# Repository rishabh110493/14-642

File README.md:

# 14-642
Work Done in Embedded Systems as a part of course

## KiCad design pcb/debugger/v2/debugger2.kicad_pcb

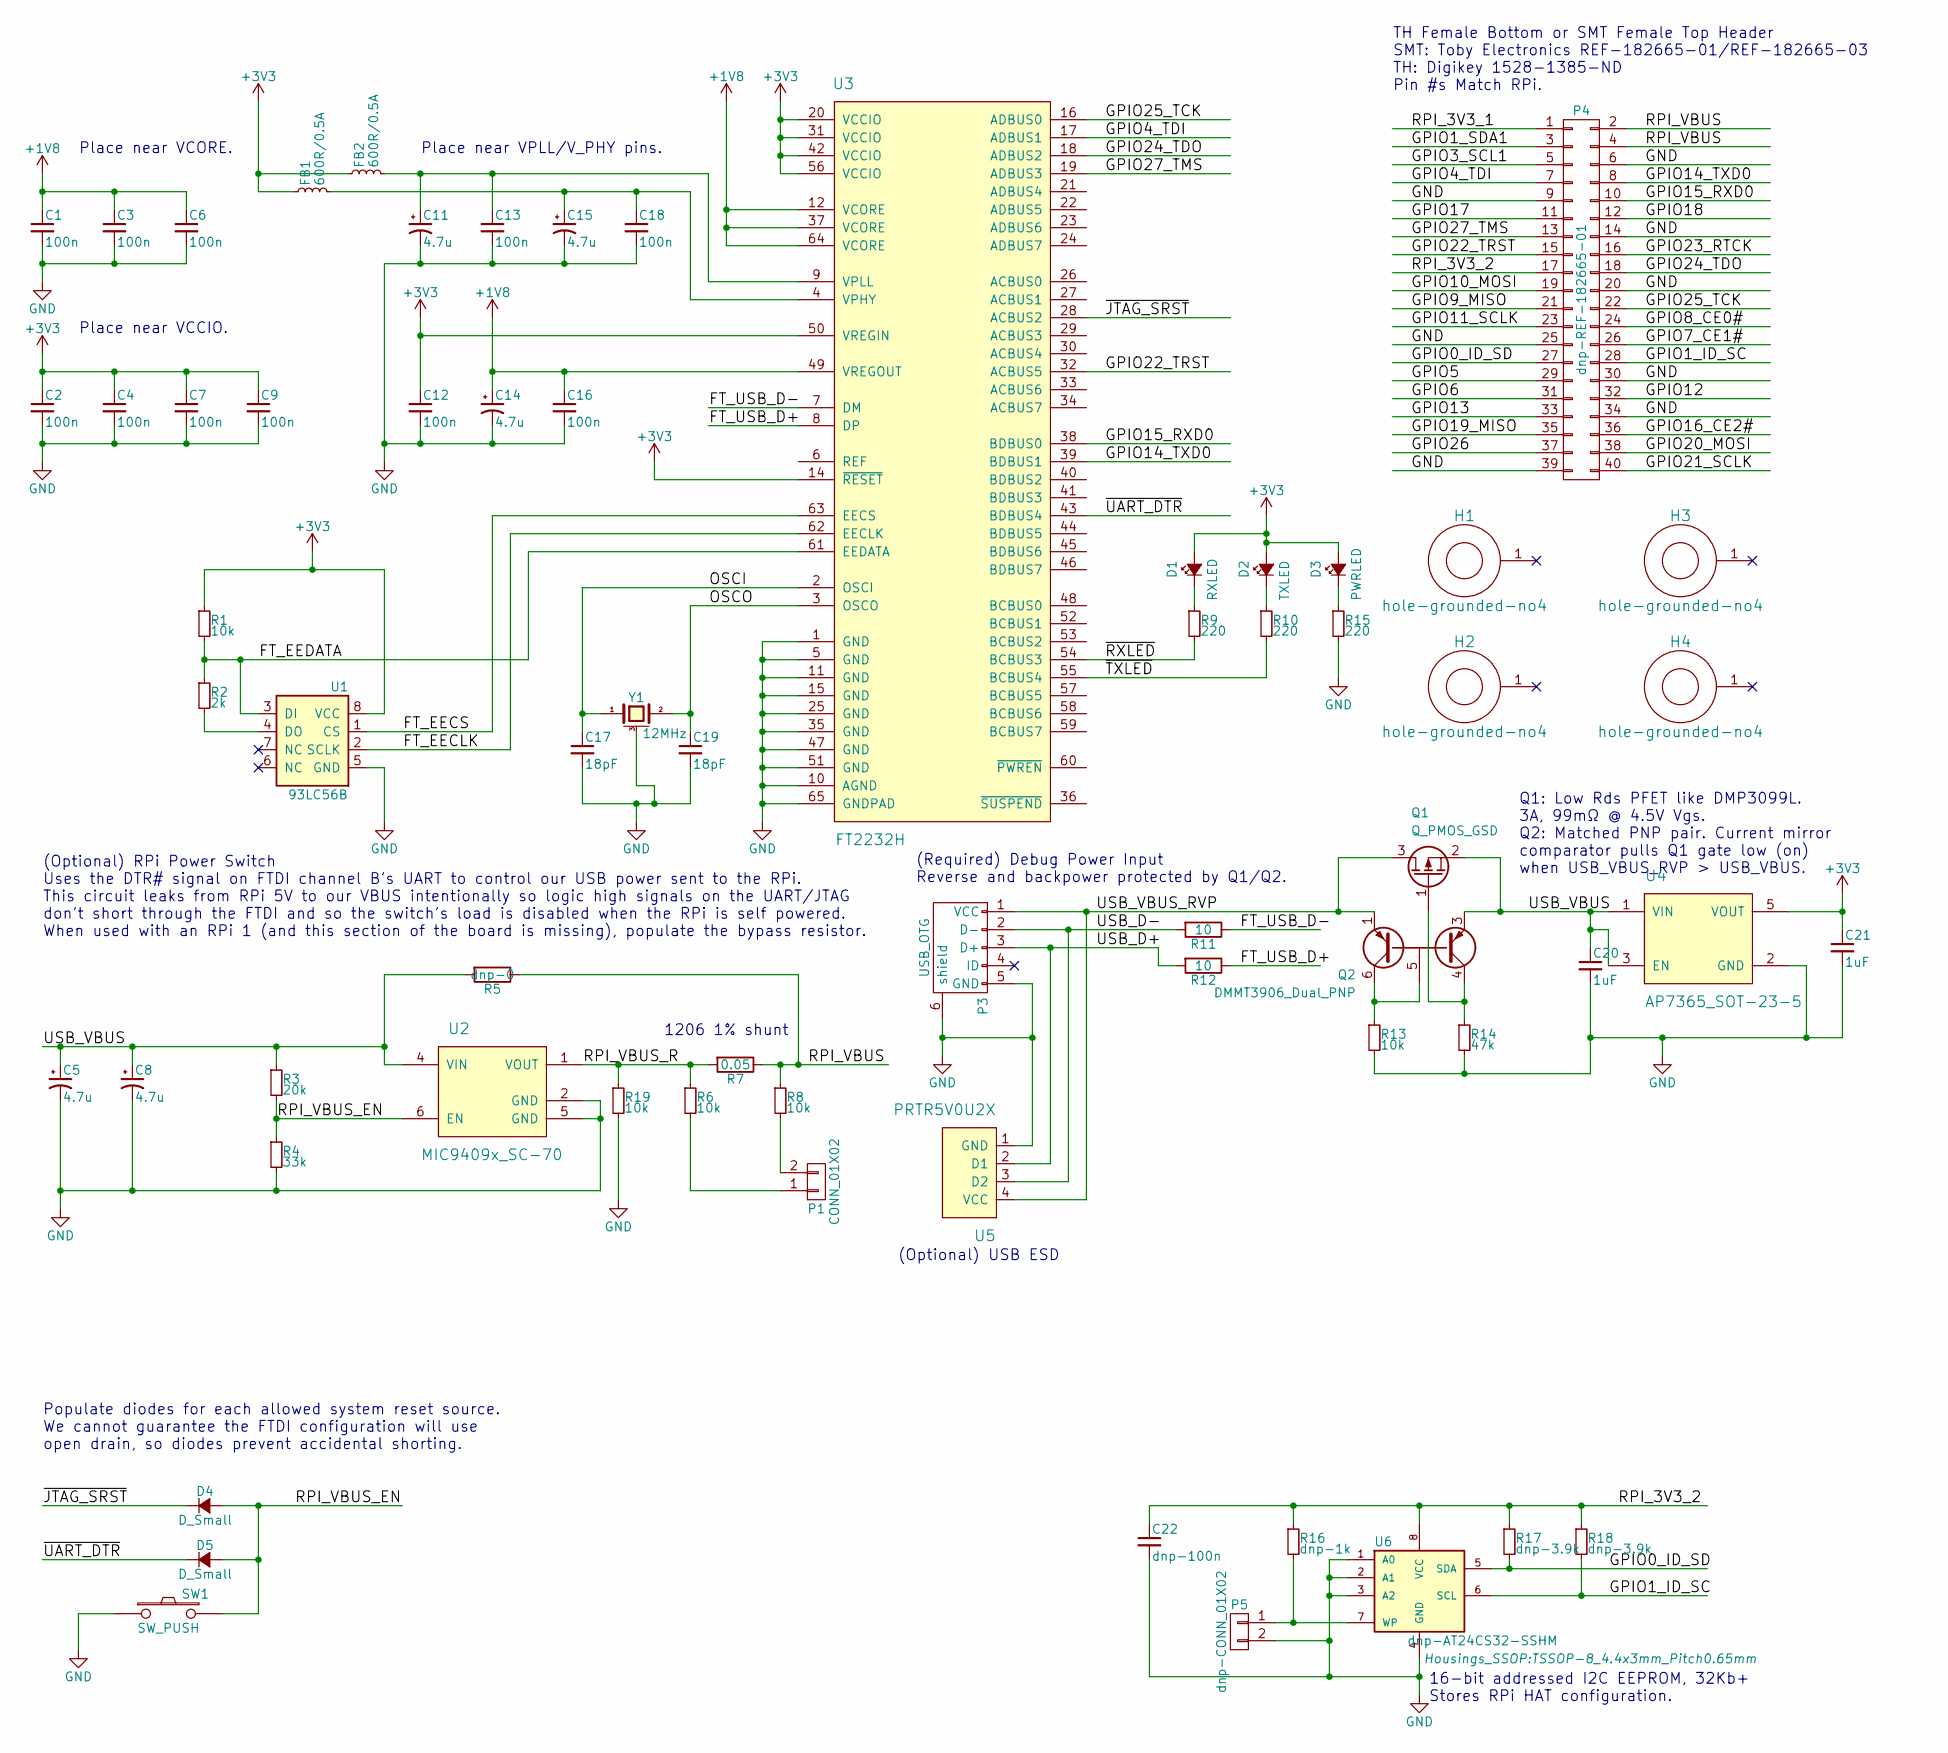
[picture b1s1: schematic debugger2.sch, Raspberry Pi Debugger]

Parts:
C1, C2, C3, C4, C6, C7, C9, C12, C13, C16, C18: 100n; C_0603
C5, C8, C11, C14, C15: 4.7u; C_1206
C17, C19: 18pF; C_0603
C20, C21: 1uF; C_0603
C22: dnp-100n; C_0603
D1: RXLED; LED-0603
D2: TXLED; LED-0603
D3: PWRLED; LED-0603
D4, D5: D_Small; SOD-523
FB1, FB2: 600R/0.5A; R_0805
H1, H2, H3, H4: hole-grounded-no4; hole-no4
P1: CONN_01X02; Pin_Header_Straight_1x02
P3: USB_OTG; USB_Micro-B_SMT
P4: dnp-REF-182665-01; Pin_Header_Straight_TH-SMT-NoPaste_2x20
P5: dnp-CONN_01X02; Pin_Header_Straight_1x02
Q1: Q_PMOS_GSD; SOT-23
Q2: DMMT3906_Dual_PNP; SOT-23-6
R1, R6, R8, R13, R19: 10k; R_0603
R2: 2k; R_0603
R3: 20k; R_0603
R4: 33k; R_0603
R5: dnp-0; R_0603
R7: 0.05; R_1206
R9, R10, R15: 220; R_0603
R11, R12: 10; R_0603
R14: 47k; R_0603
R16: dnp-1k; R_0603
R17, R18: dnp-3.9k; R_0603
SW1: SW_PUSH; SW_SPST_EVPBF
U1: 93LC56B; TSSOP-8_4.4x3mm_Pitch0.65mm
U2: MIC9409x_SC-70; SC-70-6
U3: FT2232H; TQFP-64_10x10mm_Pitch0.5mm
U4: AP7365_SOT-23-5; SOT-23-5
U5: PRTR5V0U2X; SOT-143_NXP
U6: dnp-AT24CS32-SSHM; TSSOP-8_4.4x3mm_Pitch0.65mm
Y1: 12MHz; Crystal_Grounded_3.2x2.5

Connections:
+1V8: C1.1, C3.1, C6.1, C14.1, C16.1, U3.12 (VCORE), U3.37 (VCORE), U3.49 (VREGOUT), U3.64 (VCORE)
+3V3: C2.1, C4.1, C7.1, C9.1, C12.1, C21.1, D1.2 (A), D2.2 (A), D3.2 (A), FB1.1, FB2.1, R1.1, U1.8 (VCC), U3.14 (~RESET), U3.20 (VCCIO), U3.31 (VCCIO), U3.42 (VCCIO), U3.50 (VREGIN), U3.56 (VCCIO), U4.5 (VOUT)
/FT_EECLK: U1.2 (SCLK), U3.62 (EECLK)
/FT_EECS: U1.1 (CS), U3.63 (EECS)
/FT_EEDATA: R1.2, R2.1, U1.3 (DI), U3.61 (EEDATA)
/FT_USB_D+: R12.1, U3.8 (DP)
/FT_USB_D-: R11.1, U3.7 (DM)
/GPIO0_ID_SD: P4.27, R17.2, U6.5 (SDA)
/GPIO1_ID_SC: P4.28, R18.2, U6.6 (SCL)
/GPIO1_SDA1: P4.3
/GPIO3_SCL1: P4.5
/GPIO4_TDI: P4.7, U3.17 (ADBUS1)
/GPIO5: P4.29
/GPIO6: P4.31
/GPIO7_CE1#: P4.26
/GPIO8_CE0#: P4.24
/GPIO9_MISO: P4.21
/GPIO10_MOSI: P4.19
/GPIO11_SCLK: P4.23
/GPIO12: P4.32
/GPIO13: P4.33
/GPIO14_TXD0: P4.8, U3.39 (BDBUS1)
/GPIO15_RXD0: P4.10, U3.38 (BDBUS0)
/GPIO16_CE2#: P4.36
/GPIO17: P4.11
/GPIO18: P4.12
/GPIO19_MISO: P4.35
/GPIO20_MOSI: P4.38
/GPIO21_SCLK: P4.40
/GPIO22_TRST: P4.15, U3.32 (ACBUS5)
/GPIO23_RTCK: P4.16
/GPIO24_TDO: P4.18, U3.18 (ADBUS2)
/GPIO25_TCK: P4.22, U3.16 (ADBUS0)
/GPIO26: P4.37
/GPIO27_TMS: P4.13, U3.19 (ADBUS3)
/OSCI: C17.1, U3.2 (OSCI), Y1.1
/OSCO: C19.1, U3.3 (OSCO), Y1.2
/RPI_3V3_1: P4.1
/RPI_3V3_2: C22.1, P4.17, R16.1, R17.1, R18.1, U6.8 (VCC)
/RPI_VBUS: P4.2, P4.4, R5.1, R7.1, R8.1
/RPI_VBUS_EN: D4.2 (A), D5.2 (A), R3.2, R4.1, SW1.2, U2.6 (EN)
/RPI_VBUS_R: R6.1, R7.2, R19.1, U2.1 (VOUT)
/USB_D+: P3.3 (D+), R12.2, U5.2 (D1)
/USB_D-: P3.2 (D-), R11.2, U5.3 (D2)
/USB_VBUS: C5.1, C8.1, C20.1, Q1.2 (S), Q2.3 (E2), R3.1, R5.2, U2.4 (VIN), U4.1 (VIN), U4.3 (EN)
/USB_VBUS_RVP: P3.1 (VCC), Q1.3 (D), Q2.1 (E1), U5.4 (VCC)
/~JTAG_SRST: D4.1 (K), U3.28 (ACBUS2)
/~RXLED: R9.2, U3.54 (BCBUS3)
/~TXLED: R10.2, U3.55 (BCBUS4)
/~UART_DTR: D5.1 (K), U3.43 (BDBUS4)
GND: C1.2, C2.2, C3.2, C4.2, C5.2, C6.2, C7.2, C8.2, C9.2, C11.2, C12.2, C13.2, C14.2, C15.2, C16.2, C17.2, C18.2, C19.2, C20.2, C21.2, C22.2, P3.5 (GND), P3.6 (shield), P4.6, P4.9, P4.14, P4.20, P4.25, P4.30, P4.34, P4.39, P5.2, R4.2, R13.2, R14.2, R15.2, R19.2, SW1.1, U1.5 (GND), U2.2 (GND), U2.5 (GND), U3.1 (GND), U3.5 (GND), U3.10 (AGND), U3.11 (GND), U3.15 (GND), U3.25 (GND), U3.35 (GND), U3.47 (GND), U3.51 (GND), U3.65 (GNDPAD), U4.2 (GND), U5.1 (GND), U6.1 (A0), U6.2 (A1), U6.3 (A2), U6.4 (GND), Y1.3 (case)
unnamed: C11.1, C13.1, FB2.2, U3.9 (VPLL)
unnamed: C15.1, C18.1, FB1.2, U3.4 (VPHY)
unnamed: D1.1 (K), R9.1
unnamed: D2.1 (K), R10.1
unnamed: D3.1 (K), R15.1
unnamed: P1.1, R6.2
unnamed: P1.2, R8.2
unnamed: P5.1, R16.2, U6.7 (WP)
unnamed: Q1.1 (G), Q2.4 (C2), R14.1
unnamed: Q2.5 (B), Q2.6 (C1), R13.1
unnamed: R2.2, U1.4 (DO)

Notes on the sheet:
Place near VCCIO.
Place near VCORE.
(Optional) RPi Power Switch Uses the DTR# signal on FTDI channel B's UART to control our USB power sent to the RPi. This circuit leaks from RPi 5V to our VBUS intentionally so logic high signals on the UART/JTAG don't short through the FTDI and so the switch's load is disabled when the RPi is self 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
TH Female Bottom or SMT Female Top Header SMT: Toby Electronics REF-182665-01/REF-182665-03 TH: Digikey 1528-1385-ND Pin #s Match RPi.
1206 1% shunt
(Required) Debug Power Input Reverse and backpower protected by Q1/Q2.
Q1: Low Rds PFET like DMP3099L. 3A, 99mΩ @ 4.5V Vgs. Q2: Matched PNP pair. Current mirror comparator pulls Q1 gate low (on) when USB_VBUS_RVP > USB_VBUS.
Place near VPLL/V_PHY pins.
(Optional) USB ESD
16-bit addressed I2C EEPROM, 32Kb+ Stores RPi HAT configuration.
Populate diodes for each allowed system reset source. We cannot guarantee the FTDI configuration will use open drain, so diodes prevent accidental shorting.

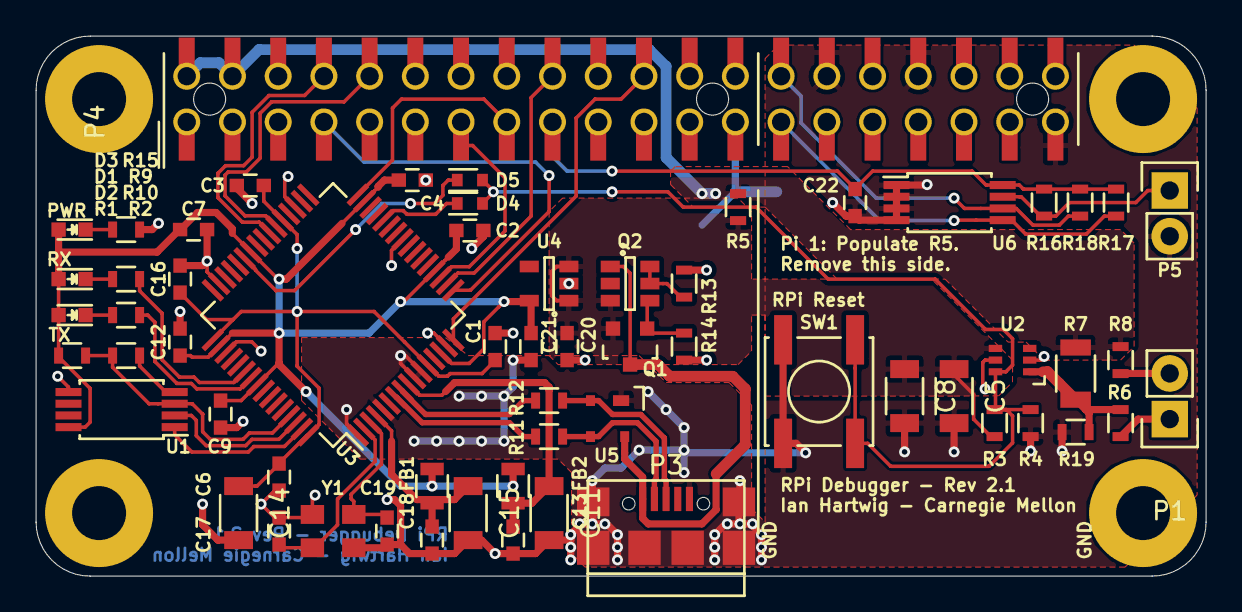
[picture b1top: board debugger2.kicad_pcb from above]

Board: 2 copper layers, 65.0 x 30.0 mm, 65 parts (0 on the bottom side), 42 nets.

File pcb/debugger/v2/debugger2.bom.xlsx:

Source | /Users/ihartwig/repos/raspberrypi-debugger/debugger2/debugger2.sch
Kicad Rev | Eeschema 4.0.0-stable
Generated Date | Wednesday | July 13 | 2016 'AMt' 02:22:38 AM
Title | Raspberry Pi Debugger
Company | Carnegie Mellon University
Revision | 2.1.2
Date Issue | Not Set
Comment | Based on FT2232H Mini Module
Comment | Drawn by: Ian Hartwig
Item # | Reference | Qty | Manufacturer | Mfg Part # | Description | Footprint | Type | Link | Value | Library | Library Ref
1 | C1, C2, C3, C4, C6, C7, C9, C12, C13, C16, C18 | 11 | Murata | GRM188R71C104KA01D | CAP CER 0.1uF ±10% 16V X7R 0603 | Capacitors_SMD:C_0603 | SMT |  | 100n | device | C_Small
2 | C17, C19 | 2 | Murata | GRM1885C1H180JA01D | CAP CER 18PF ±5% 50V NP0 0603 | Capacitors_SMD:C_0603 | SMT |  | 18pF | device | C_Small
3 | C20, C21 | 2 | Murata | GRM188R71C105KE15D | CAP CER 1UF ±10% 16V X7R 0603 | Capacitors_SMD:C_0603 | SMT |  | 1uF | device | C_Small
4 | C22 | 1 | Murata | GRM188R71C104KA01D | CAP CER 0.1uF ±10% 16V X7R 0603 | Capacitors_SMD:C_0603 | DNS |  | dnp-100n | device | C_Small
5 | C5, C8, C11, C14, C15 | 5 | AVX | 1206YG475ZAT2A | CAP CER 4.7UF -20% ~ + 80% 16V Y5V 1206 | Capacitors_SMD:C_1206 | SMT |  | 4.7u | device | CP1_Small
6 | D1, D2, D3 | 3 | Lite-On | LTST-C190GKT | LED GREEN CLEAR 0603 SMD | LEDs:LED-0603 | SMT | http://www.digikey.com/product-detail/en/LTST-C190GKT/160-11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 | RXLED | device | Led_Small
7 | D4, D5 | 2 | Toshiba | CUS520,H3F | DIODE SCHOTTKY 30V 200MA | Diodes_SMD:SOD-523 | SMT | http://www.digikey.com/product-detail/en/CUS520,H3F/CUS520H3FCT-ND/5114381 | D_Small | device | D_Small
8 | FB1, FB2 | 2 | Samsung | CIM21J202NE | FERRITE BEAD 2 KOHM 0805 | Resistors_SMD:R_0805 | SMT | http://www.digikey.com/product-detail/en/CIM21J202NE/1276-63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 | 600R/0.5A | device | L_Small
9 | P1 | 1 |  |  |  | Pin_Headers:Pin_Header_Straight_1x02 | DNS |  | CONN_01X01 | conn | CONN_01X01
10 | P3 | 1 | Amphenol-FCI | 10118192-0001LF | USB - micro B USB 2.0 Receptacle Connector 5 Position Surface Mount, Right Angl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 | debugger2-special:USB_Micro-B_SMT | SMT | http://www.digikey.com/product-detail/en/amphenol-fci/101181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 | USB_OTG | conn | USB_OTG
11 | P4 | 1 | Samtec | REF-182665-01 | 2x20 pos. with PCB alignment peg option | debugger2-special:Pin_Header_Straight_TH-SMT_2x20 | DNS | http://www.toby.co.uk/content/catalogue/products.aspx?series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 | CONN_02X20 | conn | CONN_02X20
12 | P5 | 1 |  |  |  | Pin_Headers:Pin_Header_Straight_1x02 | DNS |  | dnp-CONN_01X02 | conn | CONN_01X02
13 | Q1 | 1 | Diodes Inc | DMP3099L-7 | MOSFET P-CH 30V SOT23 | TO_SOT_Packages_SMD:SOT-23 | SMT | http://www.digikey.com/product-detail/en/DMP3099L-7/DMP3099L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 | Q_PMOS_GSD | device | Q_PMOS_GSD
14 | Q2 | 1 | Diodes Inc | DMMT3906-7-F | TRANS 2PNP 40V 0.2A SOT26 | TO_SOT_Packages_SMD:SOT-23-6 | SMT | http://www.digikey.com/product-detail/en/DMMT3906-7-F/DMMT39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 | DMMT3906_Dual_PNP | debugger2-special | DMMT3906_Dual_PNP
15 | R1, R6, R8, R13, R19 | 5 | Vishay Dale | CRCW060310K0FKEA | RES SMD 10K OHM 1% 1/10W 0603 | Resistors_SMD:R_0603 | SMT |  | 10k | device | R_Small
16 | R11, R12 | 2 | Vishay Dale | CRCW060310R0FKEA | RES SMD 10 OHM 1% 1/10W 0603 | Resistors_SMD:R_0603 | SMT |  | 10 | device | R
17 | R14 | 1 | Vishay Dale | CRCW060347K0FKEA | RES SMD 47K OHM 1% 1/10W 0603 | Resistors_SMD:R_0603 | SMT | http://www.digikey.com/product-detail/en/vishay-dale/CRCW060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 | 47k | device | R_Small
18 | R16 | 1 | Vishay Dale | CRCW06031K00FKEA | RES SMD 1K OHM 1% 1/10W 0603 | Resistors_SMD:R_0603 | DNS |  | dnp-1k | device | R_Small
19 | R17, R18 | 2 | Vishay Dale | CRCW06033K90FKEA | RES SMD 3.9K OHM 1% 1/10W 0603 | Resistors_SMD:R_0603 | DNS |  | dnp-3.9k | device | R_Small
20 | R2 | 1 | Vishay Dale | CRCW06032K00FKEA | RES SMD 2K OHM 1% 1/10W 0603 | Resistors_SMD:R_0603 | SMT |  | 2k | device | R_Small
21 | R3 | 1 | Vishay Dale | CRCW060320K0FKEA | RES SMD 20K OHM 1% 1/10W 0603 | Resistors_SMD:R_0603 | SMT |  | 20k | device | R_Small
22 | R4 | 1 | Vishay Dale | CRCW060333K0FKEA | RES SMD 33K OHM 1% 1/10W 0603 | Resistors_SMD:R_0603 | SMT |  | 33k | device | R_Small
23 | R5 | 1 |  |  |  | Resistors_SMD:R_0603 | DNS |  | dnp-0 | device | R
24 | R7 | 1 | Stackpole Electronics | CSR1206FT50L0 | RES SMD 0.05 OHM 1% 1/2W 1206 | Resistors_SMD:R_1206 | SMT | http://www.digikey.com/product-detail/en/stackpole-electroni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 | 0.01 | device | R
25 | R9, R10, R15 | 3 | Vishay Dale | CRCW0603220RFKEA | RES SMD 220 OHM 1% 1/10W 0603 | Resistors_SMD:R_0603 | SMT | http://www.digikey.com/product-detail/en/vishay-dale/CRCW060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 | 220 | device | R_Small
26 | SW1 | 1 | TE Connectivity | FSMCTTR | SWITCH TACTILE SPST-NO 0.02A 15V | Buttons_Switches_SMD:SW_SPST_EVPBF | SMT | http://www.digikey.com/product-detail/en/FSMCTTR/450-2133-1-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 | SW_PUSH | device | SW_PUSH
27 | U1 | 1 | Microchip | 93LC56B-I/ST | IC EEPROM 2KBIT 2MHZ 8TSSOP | Housings_SSOP:TSSOP-8_4.4x3mm_Pitch0.65mm | SMT | http://www.digikey.com/product-detail/en/93LC56B-I%2FST/93LC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 | 93LC56B | memory | 93LCxxA
28 | U2 | 1 | Microchip | MIC94093YC6-TR | IC LOAD SW HGH SIDE 1.2A SC70-6 | TO_SOT_Packages_SMD:SC-70-6 | SMT | http://www.digikey.com/product-detail/en/MIC94093YC6-TR/576-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 | MIC9409x_SC-70 | debugger2-special | MIC9409x_SC-70
29 | U3 | 1 | FTDI | FT2232HL | IC USB HS DUAL UART/FIFO 64-LQFP | Housings_QFP:TQFP-64_10x10mm_Pitch0.5mm | SMT | http://www.digikey.com/product-detail/en/FT2232HL-REEL/768-1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 | FT2232H | debugger2-special | FT2232H
30 | U4 | 1 | Diodes Inc | AP7365-33WG-7 | IC REG LDO 3.3V 0.6A SOT-25 | TO_SOT_Packages_SMD:SOT-23-5 | SMT | http://www.digikey.com/product-detail/en/AP7365-33WG-7/AP736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 | AP7365_SOT-23-5 | debugger2-special | AP7365_SOT-23-5
31 | U5 | 1 | NXP | PRTR5V0U2X,215 | TVS DIODE 5.5VWM SOT143B | debugger2-special:SOT-143_NXP | SMT | http://www.digikey.com/product-detail/en/PRTR5V0U2X,215/568-4140-1-ND/1589981 | PRTR5V0U2X | debugger2-special | PRTR5V0U2X
32 | U6 | 1 |  |  |  | Housings_SSOP:TSSOP-8_4.4x3mm_Pitch0.65mm | DNS |  | dnp-AT24CS32-SSHM | memory | AT24CS32-SSHM
33 | Y1 | 1 | Abracon LLC | ABM8-12.000MHZ-B2-T | 12MHz ±20ppm Crystal 18pF 120 Ohm -20°C ~ 70°C Surface Mount 4-SMD, No Lead (DF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 | debugger2-special:Crystal_Grounded_3.2x2.5 | SMT | http://www.digikey.com/product-detail/en/ABM8-12.000MHZ-B2-T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 | 12MHz | device | CRYSTAL_SMD

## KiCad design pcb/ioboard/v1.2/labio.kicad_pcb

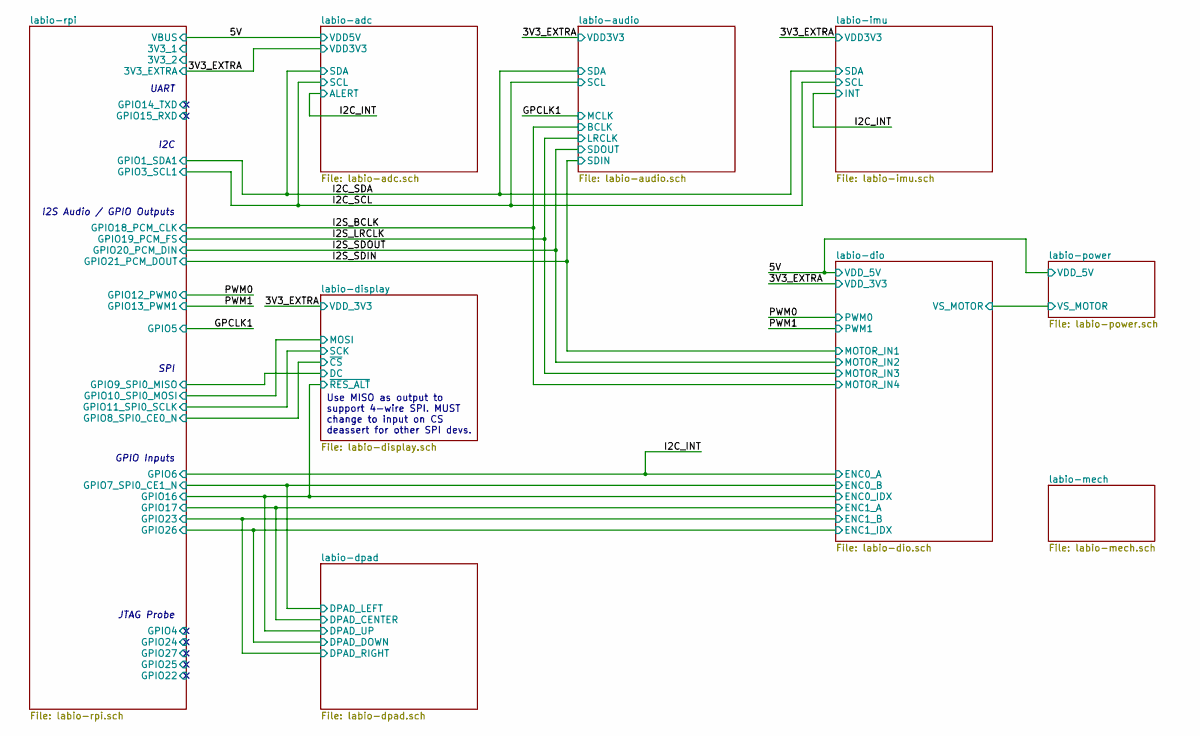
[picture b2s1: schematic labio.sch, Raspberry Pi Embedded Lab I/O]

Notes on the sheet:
JTAG Probe
GPIO Inputs
I2S Audio / GPIO Outputs
I2C
UART
SPI
Use MISO as output to support 4-wire SPI. MUST change to input on CS deassert for other SPI devs.

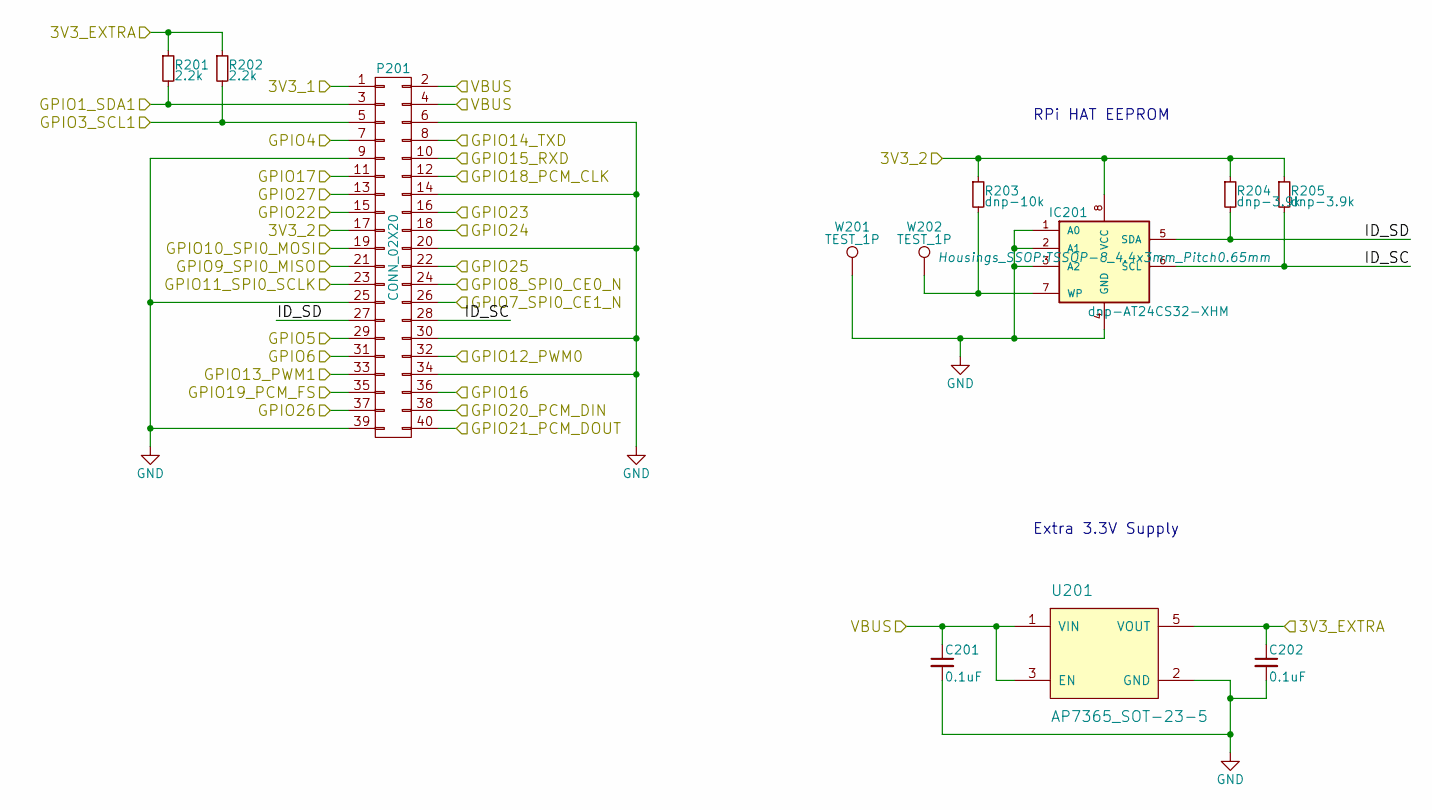
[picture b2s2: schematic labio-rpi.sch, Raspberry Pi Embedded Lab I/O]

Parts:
C201, C202: 0.1uF; C_0603
IC201: dnp-AT24CS32-XHM; TSSOP-8_4.4x3mm_Pitch0.65mm
P201: CONN_02X20; Pin_Header_Straight_TH-SMT-NoPaste_2x20
R201, R202: 2.2k; R_0603
R203: dnp-10k; R_0603
R204, R205: dnp-3.9k; R_0603
U201: AP7365_SOT-23-5; SOT-23-5
W201, W202: TEST_1P; Measurement_Point_Round-SMD-Pad_Small

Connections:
/3V3_EXTRA: C202.1, R201.1, R202.1, U201.5 (VOUT); also elsewhere on the board
/5V: C201.1, P201.2, P201.4, U201.1 (VIN), U201.3 (EN); also elsewhere on the board
/GPCLK1: P201.29; also elsewhere on the board
/I2C_INT: P201.31; also elsewhere on the board
/I2C_SCL: P201.5, R202.2; also elsewhere on the board
/I2C_SDA: P201.3, R201.2; also elsewhere on the board
/I2S_BCLK: P201.12; also elsewhere on the board
/I2S_LRCLK: P201.35; also elsewhere on the board
/I2S_SDIN: P201.40; also elsewhere on the board
/I2S_SDOUT: P201.38; also elsewhere on the board
/PWM0: P201.32; also elsewhere on the board
/PWM1: P201.33; also elsewhere on the board
/labio-display/DC: P201.21; also elsewhere on the board
/labio-dpad/DPAD_CENTER: P201.11; also elsewhere on the board
/labio-dpad/DPAD_DOWN: P201.37; also elsewhere on the board
/labio-dpad/DPAD_LEFT: P201.26; also elsewhere on the board
/labio-dpad/DPAD_RIGHT: P201.16; also elsewhere on the board
/labio-dpad/DPAD_UP: P201.36; also elsewhere on the board
/labio-rpi/3V3_1: P201.1
/labio-rpi/3V3_2: IC201.8 (VCC), P201.17, R203.1, R204.1, R205.1
/labio-rpi/GPIO4: P201.7
/labio-rpi/GPIO8_SPI0_CE0_N: P201.24; also elsewhere on the board
/labio-rpi/GPIO10_SPI0_MOSI: P201.19; also elsewhere on the board
/labio-rpi/GPIO11_SPI0_SCLK: P201.23; also elsewhere on the board
/labio-rpi/GPIO14_TXD: P201.8
/labio-rpi/GPIO15_RXD: P201.10
/labio-rpi/GPIO22: P201.15
/labio-rpi/GPIO24: P201.18
/labio-rpi/GPIO25: P201.22
/labio-rpi/GPIO27: P201.13
/labio-rpi/ID_SC: IC201.6 (SCL), P201.28, R205.2
/labio-rpi/ID_SD: IC201.5 (SDA), P201.27, R204.2
GND: C201.2, C202.2, IC201.1 (A0), IC201.2 (A1), IC201.3 (A2), IC201.4 (GND), P201.6, P201.9, P201.14, P201.20, P201.25, P201.30, P201.34, P201.39, U201.2 (GND), W201.1; also elsewhere on the board
unnamed: IC201.7 (WP), R203.2, W202.1

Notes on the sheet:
RPi HAT EEPROM
Extra 3.3V Supply

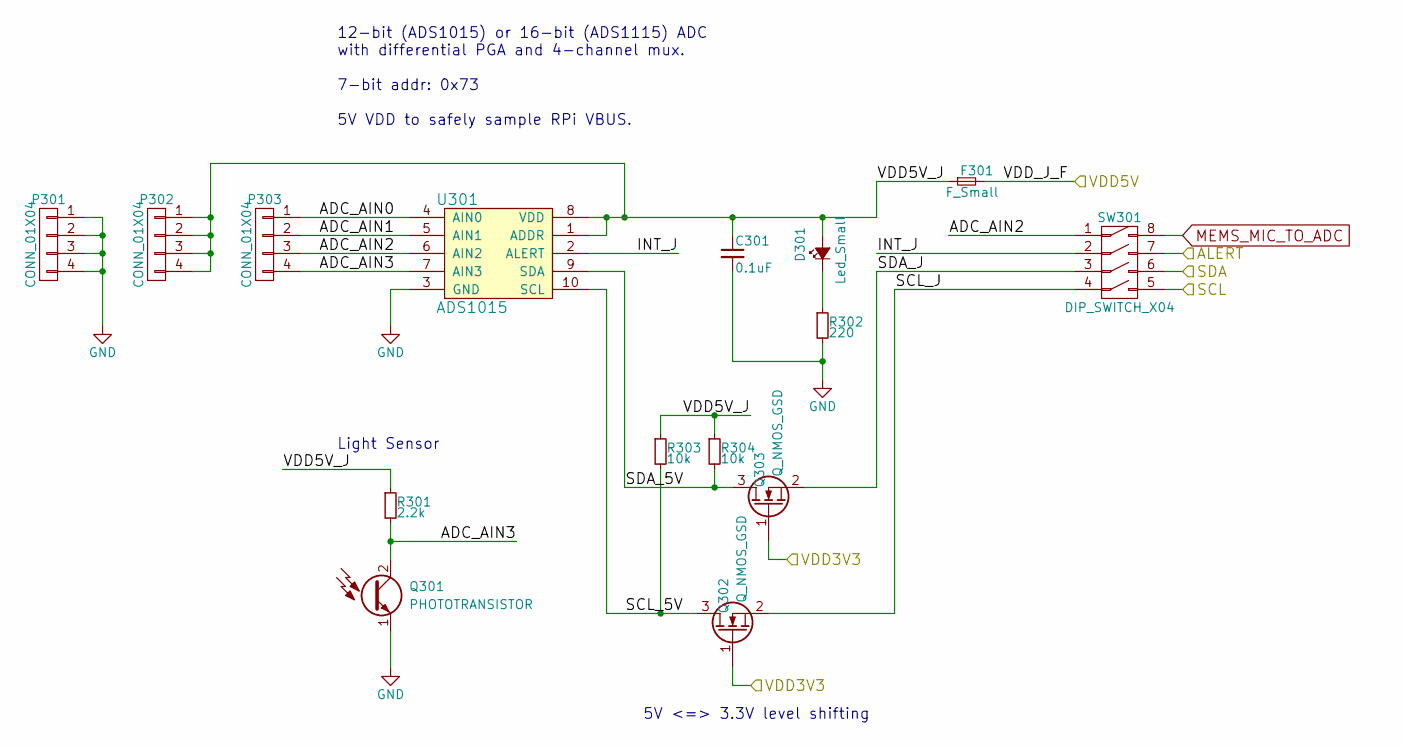
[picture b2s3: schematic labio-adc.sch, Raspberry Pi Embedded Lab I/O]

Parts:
C301: 0.1uF; C_0603
D301: Led_Small; LED-0603
F301: F_Small; R_1206
P301, P302, P303: CONN_01X04; Pin_Header_Straight_1x04
Q301: PHOTOTRANSISTOR; LED-0603
Q302, Q303: Q_NMOS_GSD; SOT-23
R301: 2.2k; R_0603
R302: 220; R_0603
R303, R304: 10k; R_0603
SW301: DIP_SWITCH_X04; DIP-8_W7.62mm_SMT
U301: ADS1015; MSOP-10_3x3mm_Pitch0.5mm

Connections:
/3V3_EXTRA: Q302.1 (G), Q303.1 (G); also elsewhere on the board
/5V: F301.2; also elsewhere on the board
/I2C_INT: SW301.7 (2A); also elsewhere on the board
/I2C_SCL: SW301.5 (4B); also elsewhere on the board
/I2C_SDA: SW301.6 (3B); also elsewhere on the board
/labio-adc/ADC_AIN0: P303.1, U301.4 (AIN0)
/labio-adc/ADC_AIN1: P303.2, U301.5 (AIN1)
/labio-adc/ADC_AIN2: P303.3, SW301.1 (1A), U301.6 (AIN2)
/labio-adc/ADC_AIN3: P303.4, Q301.2 (C), R301.2, U301.7 (AIN3)
/labio-adc/INT_J: SW301.2 (2A), U301.2 (ALERT)
/labio-adc/SCL_5V: Q302.3 (D), R303.2, U301.10 (SCL)
/labio-adc/SCL_J: Q302.2 (S), SW301.4 (4A)
/labio-adc/SDA_5V: Q303.3 (D), R304.2, U301.9 (SDA)
/labio-adc/SDA_J: Q303.2 (S), SW301.3 (3A)
/labio-adc/VDD5V_J: C301.1, D301.2 (A), F301.1, P302.1, P302.2, P302.3, P302.4, R301.1, R303.1, R304.1, U301.1 (ADDR), U301.8 (VDD)
GND: C301.2, P301.1, P301.2, P301.3, P301.4, Q301.1 (E), R302.2, U301.3 (GND); also elsewhere on the board
MEMS_MIC_TO_ADC: SW301.8 (1B); also elsewhere on the board
unnamed: D301.1 (K), R302.1

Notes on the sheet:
12-bit (ADS1015) or 16-bit (ADS1115) ADC with differential PGA and 4-channel mux. 7-bit addr: 0x73 5V VDD to safely sample RPi VBUS.
Light Sensor
5V <=> 3.3V level shifting

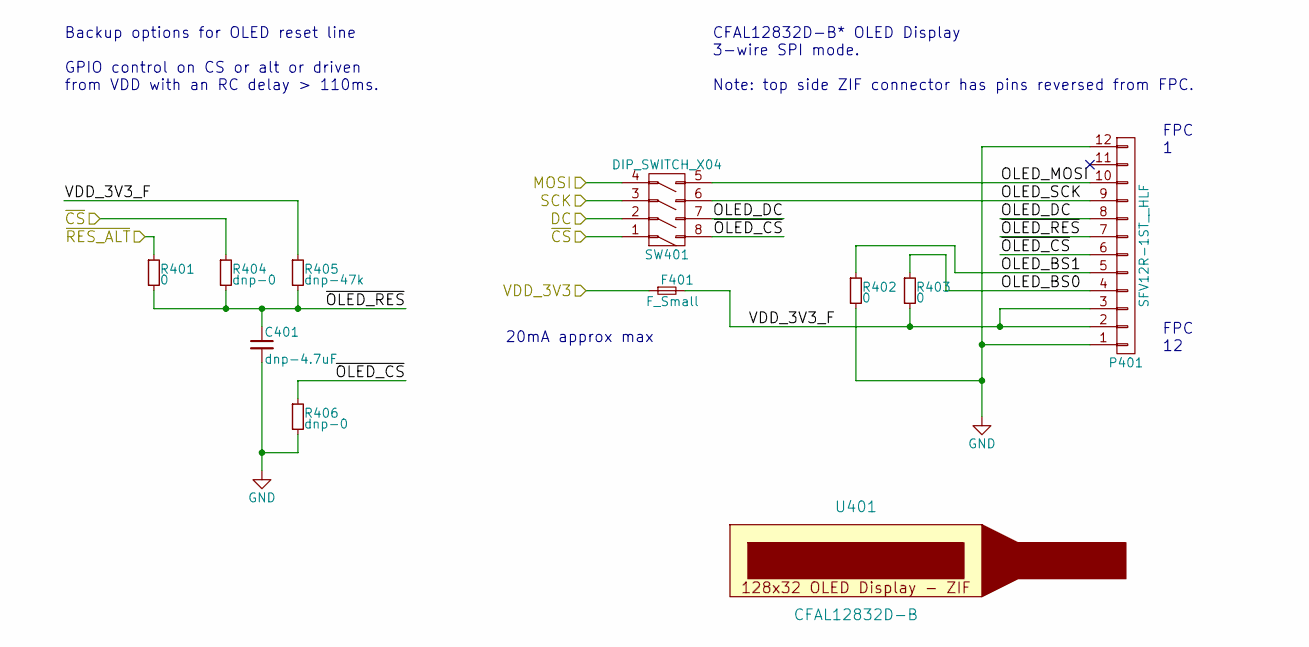
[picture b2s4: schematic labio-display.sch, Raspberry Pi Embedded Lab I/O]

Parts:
C401: dnp-4.7uF; C_0805
F401: F_Small; R_1206
P401: SFV12R-1ST__HLF; SFVxxR-xSTxxHLF
R401, R402, R403: 0; R_0603
R404, R406: dnp-0; R_0603
R405: dnp-47k; R_0603
SW401: DIP_SWITCH_X04; DIP-8_W7.62mm_SMT
U401: CFAL12832D-B

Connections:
/3V3_EXTRA: F401.1; also elsewhere on the board
/labio-display/DC: SW401.2 (2A); also elsewhere on the board
/labio-display/OLED_BS0: P401.4, R403.1
/labio-display/OLED_BS1: P401.5, R402.1
/labio-display/OLED_DC: P401.8, SW401.7 (2A)
/labio-display/OLED_MOSI: P401.10, SW401.5 (4B)
/labio-display/OLED_SCK: P401.9, SW401.6 (3B)
/labio-display/VDD_3V3_F: F401.2, P401.2, P401.3, R403.2, R405.1
/labio-display/~OLED_CS: P401.6, R406.1, SW401.8 (1B)
/labio-display/~OLED_RES: C401.1, P401.7, R401.2, R404.2, R405.2
/labio-dpad/DPAD_UP: R401.1; also elsewhere on the board
/labio-rpi/GPIO8_SPI0_CE0_N: R404.1, SW401.1 (1A); also elsewhere on the board
/labio-rpi/GPIO10_SPI0_MOSI: SW401.4 (4A); also elsewhere on the board
/labio-rpi/GPIO11_SPI0_SCLK: SW401.3 (3A); also elsewhere on the board
GND: C401.2, P401.1, P401.12, R402.2, R406.2; also elsewhere on the board

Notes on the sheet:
CFAL12832D-B* OLED Display 3-wire SPI mode. Note: top side ZIF connector has pins reversed from FPC.
20mA approx max
FPC 1
FPC 12
Backup options for OLED reset line GPIO control on CS or alt or driven from VDD with an RC delay > 110ms.

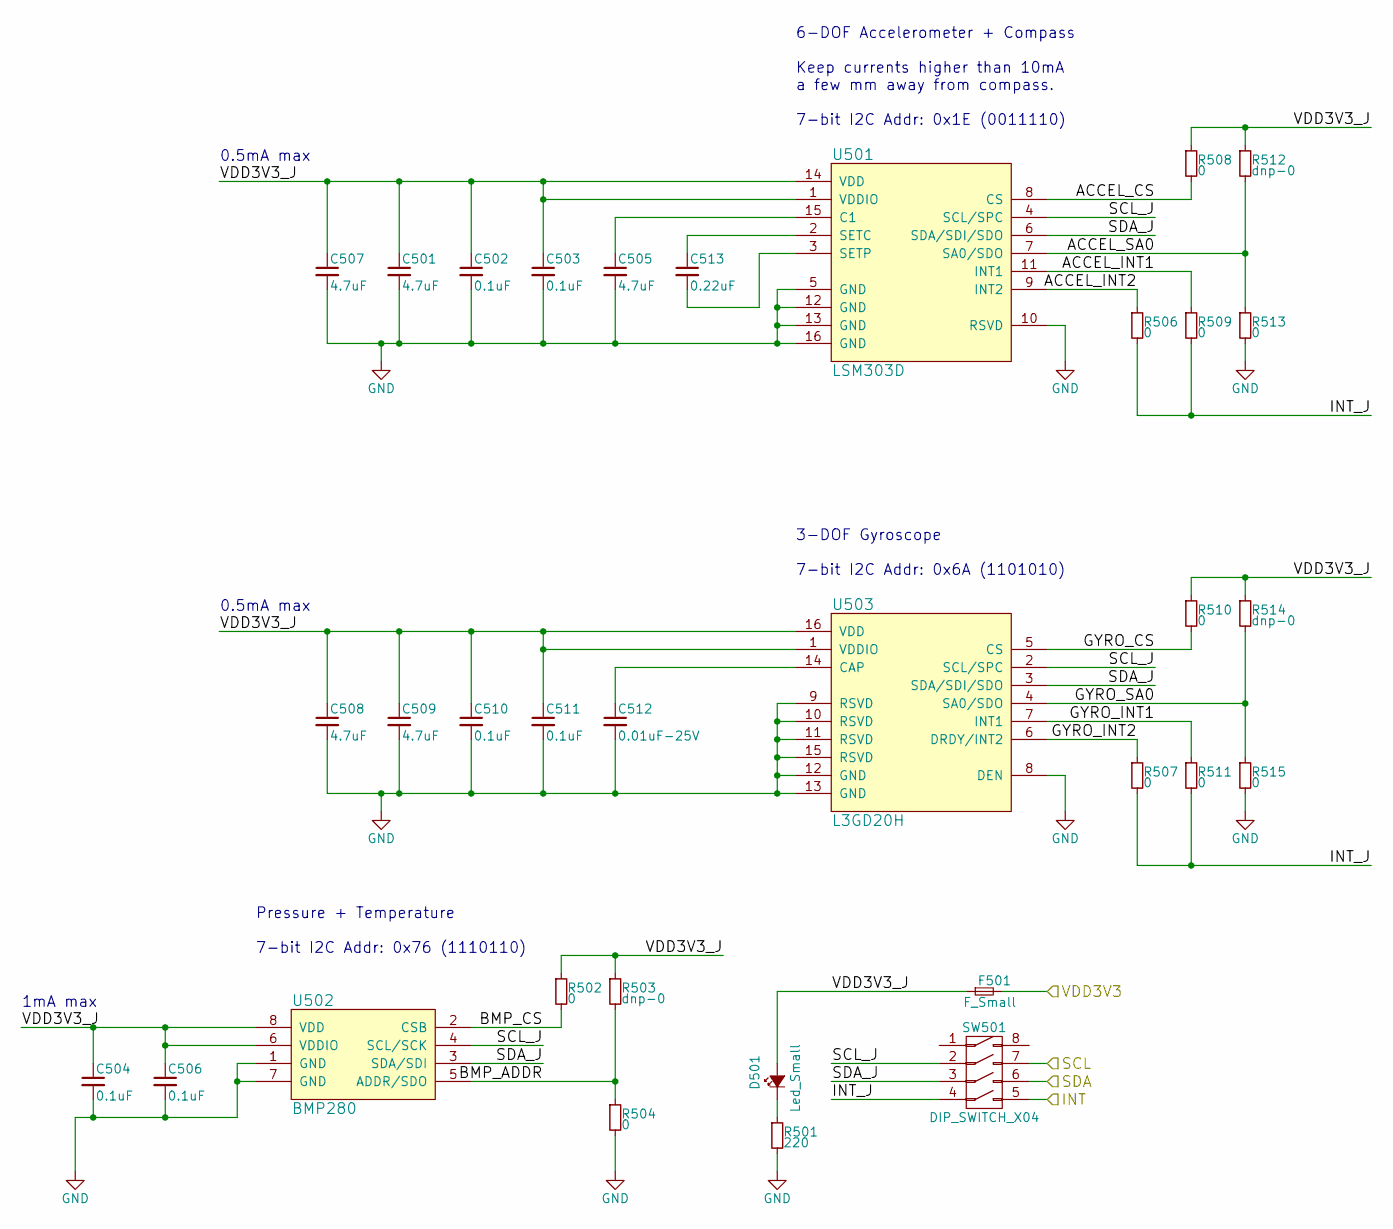
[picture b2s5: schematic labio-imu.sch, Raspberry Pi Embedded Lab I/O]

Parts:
C501, C505, C507, C508, C509: 4.7uF; C_0805
C502, C503, C504, C506, C510, C511: 0.1uF; C_0603
C512: 0.01uF-25V; C_0603
C513: 0.22uF; C_0603
D501: Led_Small; LED-0603
F501: F_Small; R_1206
R501: 220; R_0603
R502, R504, R506, R507, R508, R509, R510, R511, R513, R515: 0; R_0603
R503, R512, R514: dnp-0; R_0603
SW501: DIP_SWITCH_X04; DIP-8_W7.62mm_SMT
U501: LSM303D; LGA-16_3x3mm_Pitch0.5mm_ST
U502: BMP280; LGA-8_2.5x2.0mm_Pitch0.65mm_BMx280
U503: L3GD20H; LGA-16_3x3mm_Pitch0.5mm_ST

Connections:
/3V3_EXTRA: F501.2; also elsewhere on the board
/I2C_INT: SW501.5 (4B); also elsewhere on the board
/I2C_SCL: SW501.7 (2A); also elsewhere on the board
/I2C_SDA: SW501.6 (3B); also elsewhere on the board
/labio-imu/ACCEL_CS: R508.2, U501.8 (CS)
/labio-imu/ACCEL_INT1: R509.1, U501.11 (INT1)
/labio-imu/ACCEL_INT2: R506.1, U501.9 (INT2)
/labio-imu/ACCEL_SA0: R512.2, R513.1, U501.7 (SA0/SDO)
/labio-imu/BMP_ADDR: R503.2, R504.1, U502.5 (ADDR/SDO)
/labio-imu/BMP_CS: R502.2, U502.2 (CSB)
/labio-imu/GYRO_CS: R510.2, U503.5 (CS)
/labio-imu/GYRO_INT1: R511.1, U503.7 (INT1)
/labio-imu/GYRO_INT2: R507.1, U503.6 (DRDY/INT2)
/labio-imu/GYRO_SA0: R514.2, R515.1, U503.4 (SA0/SDO)
/labio-imu/INT_J: R506.2, R507.2, R509.2, R511.2, SW501.4 (4A)
/labio-imu/SCL_J: SW501.2 (2A), U501.4 (SCL/SPC), U502.4 (SCL/SCK), U503.2 (SCL/SPC)
/labio-imu/SDA_J: SW501.3 (3A), U501.6 (SDA/SDI/SDO), U502.3 (SDA/SDI), U503.3 (SDA/SDI/SDO)
/labio-imu/VDD3V3_J: C501.1, C502.1, C503.1, C504.1, C506.1, C507.1, C508.1, C509.1, C510.1, C511.1, D501.2 (A), F501.1, R502.1, R503.1, R508.1, R510.1, R512.1, R514.1, U501.1 (VDDIO), U501.14 (VDD), U502.6 (VDDIO), U502.8 (VDD), U503.1 (VDDIO), U503.16 (VDD)
GND: C501.2, C502.2, C503.2, C504.2, C505.2, C506.2, C507.2, C508.2, C509.2, C510.2, C511.2, C512.2, R501.2, R504.2, R513.2, R515.2, U501.5 (GND), U501.10 (RSVD), U501.12 (GND), U501.13 (GND), U501.16 (GND), U502.1 (GND), U502.7 (GND), U503.8 (DEN), U503.9 (RSVD), U503.10 (RSVD), U503.11 (RSVD), U503.12 (GND), U503.13 (GND), U503.15 (RSVD); also elsewhere on the board
unnamed: C505.1, U501.15 (C1)
unnamed: C512.1, U503.14 (CAP)
unnamed: C513.1, U501.2 (SETC)
unnamed: C513.2, U501.3 (SETP)
unnamed: D501.1 (K), R501.1

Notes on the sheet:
6-DOF Accelerometer + Compass Keep currents higher than 10mA a few mm away from compass. 7-bit I2C Addr: 0x1E (0011110)
Pressure + Temperature 7-bit I2C Addr: 0x76 (1110110)
0.5mA max
1mA max
3-DOF Gyroscope 7-bit I2C Addr: 0x6A (1101010)
